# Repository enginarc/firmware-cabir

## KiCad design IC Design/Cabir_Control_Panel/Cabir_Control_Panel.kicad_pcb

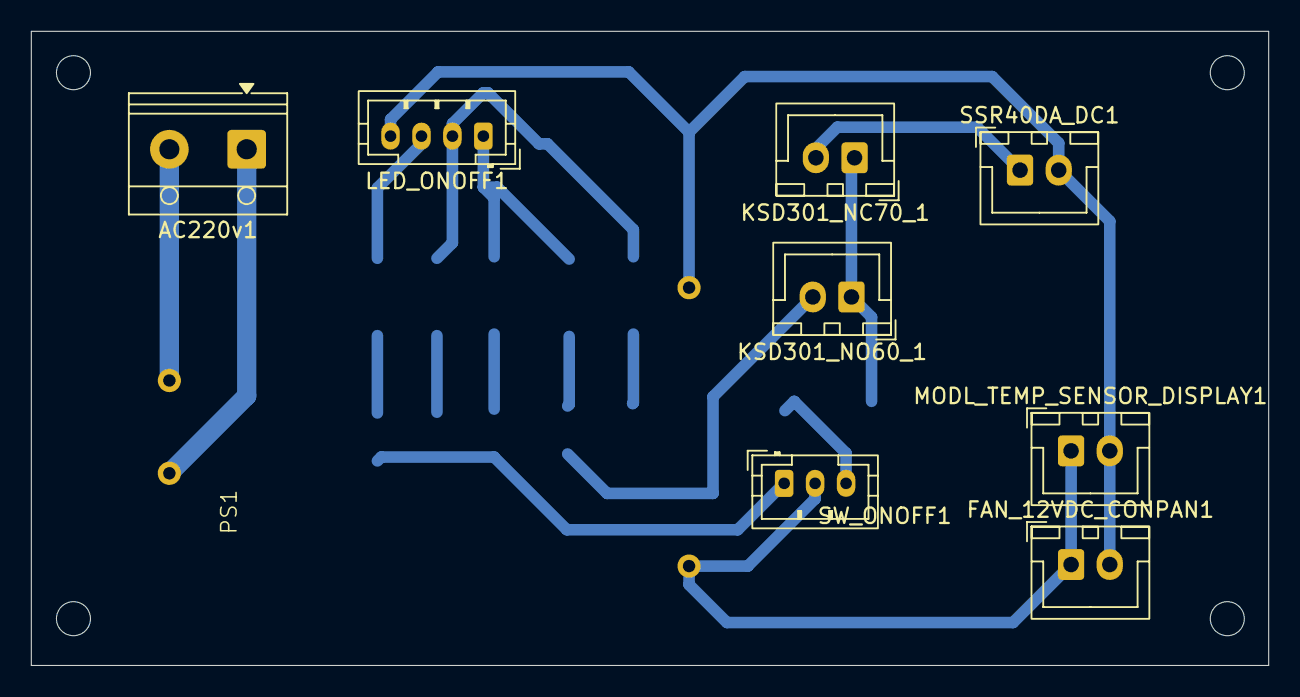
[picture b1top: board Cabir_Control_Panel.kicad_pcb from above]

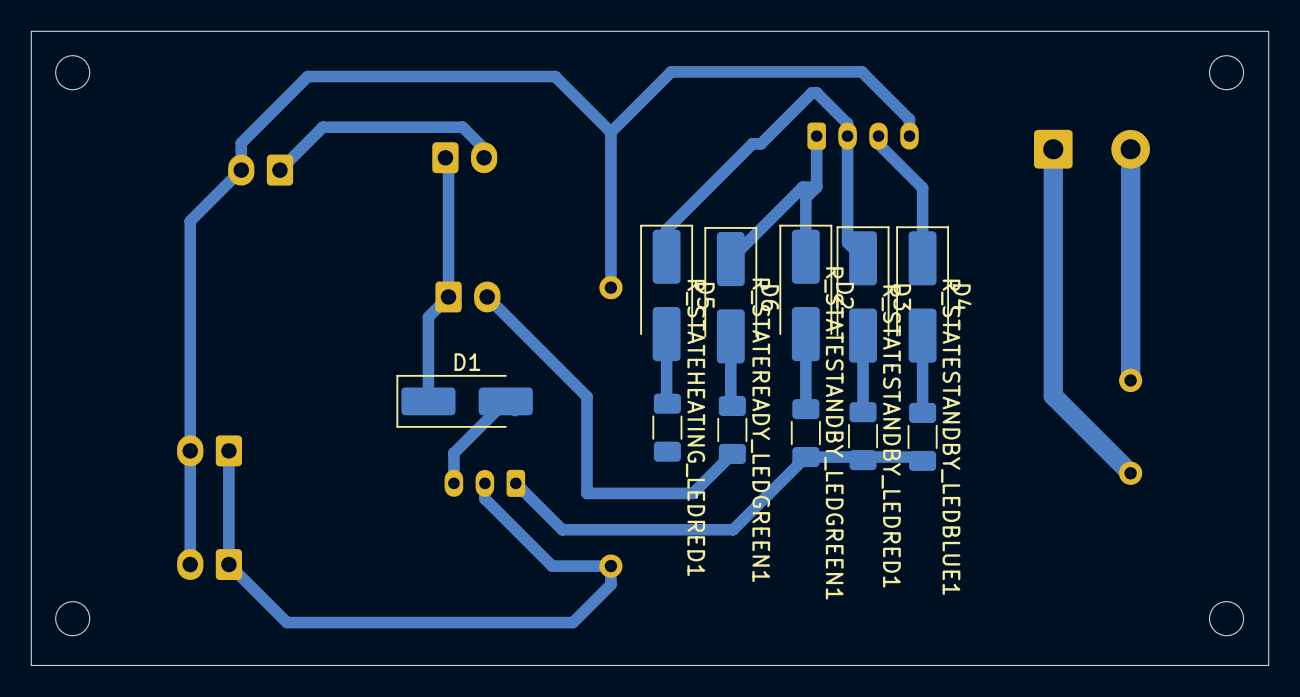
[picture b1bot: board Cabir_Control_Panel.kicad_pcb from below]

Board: 2 copper layers, 80.0 x 41.0 mm, 20 parts (11 on the bottom side), 17 nets.

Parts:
AC220v1: Screw_Terminal_01x02; TerminalBlock_RND_205-00012_1x02_P5.00mm_Horizontal
D1, D2, D3, D4, D5, D6: M7; D_SMA_Handsoldering
FAN_12VDC_CONPAN1: Conn_01x02_Pin; JST_XH_B2B-XH-A_1x02_P2.50mm_Vertical
KSD301_NC70_1, KSD301_NO60_1: Conn_01x02_Pin; JST_XH_B2B-XH-A_1x02_P2.50mm_Vertical
LED_ONOFF1: Conn_01x04_Pin; JST_PH_B4B-PH-K_1x04_P2.00mm_Vertical
MODL_TEMP_SENSOR_DISPLAY1: Conn_01x02_Pin; JST_XH_B2B-XH-A_1x02_P2.50mm_Vertical
PS1: HLK-5M12_PCB_AC-DC_Adapter
R_STATEHEATING_LEDRED1: 470R; R_1206_3216Metric_Pad1.30x1.75mm_HandSolder
R_STATEREADY_LEDGREEN1: 470R; R_1206_3216Metric_Pad1.30x1.75mm_HandSolder
R_STATESTANDBY_LEDBLUE1: 1.2k; R_1206_3216Metric_Pad1.30x1.75mm_HandSolder
R_STATESTANDBY_LEDGREEN1: 470R; R_1206_3216Metric_Pad1.30x1.75mm_HandSolder
R_STATESTANDBY_LEDRED1: 470R; R_1206_3216Metric_Pad1.30x1.75mm_HandSolder
SSR40DA_DC1: Conn_01x02_Pin; JST_XH_B2B-XH-A_1x02_P2.50mm_Vertical
SW_ONOFF1: Conn_01x03_Pin; JST_PH_B3B-PH-K_1x03_P2.00mm_Vertical

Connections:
/12V+: FAN_12VDC_CONPAN1.1, MODL_TEMP_SENSOR_DISPLAY1.1, PS1.4 (+Vout), SW_ONOFF1.2
/BLUE+: D4.1 (K), LED_ONOFF1.3
/GREEN+: D2.1 (K), D6.1 (K), LED_ONOFF1.1
/OFF+: R_STATESTANDBY_LEDBLUE1.2, R_STATESTANDBY_LEDGREEN1.2, R_STATESTANDBY_LEDRED1.2, SW_ONOFF1.1
/ON+: D1.2 (A), SW_ONOFF1.3
/RED+: D3.1 (K), D5.1 (K), LED_ONOFF1.2
GND: FAN_12VDC_CONPAN1.2, LED_ONOFF1.4, MODL_TEMP_SENSOR_DISPLAY1.2, PS1.3 (-Vout), SSR40DA_DC1.2
unnamed: AC220v1.2, PS1.1 (AC_(L))
unnamed: AC220v1.1, PS1.2 (AC_(N))
unnamed: D1.1 (K), KSD301_NC70_1.1, KSD301_NO60_1.1
unnamed: D2.2 (A), R_STATESTANDBY_LEDGREEN1.1
unnamed: D3.2 (A), R_STATESTANDBY_LEDRED1.1
unnamed: D4.2 (A), R_STATESTANDBY_LEDBLUE1.1
unnamed: D5.2 (A), R_STATEHEATING_LEDRED1.1
unnamed: D6.2 (A), R_STATEREADY_LEDGREEN1.1
unnamed: KSD301_NC70_1.2, R_STATEHEATING_LEDRED1.2, SSR40DA_DC1.1
unnamed: KSD301_NO60_1.2, R_STATEREADY_LEDGREEN1.2

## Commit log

2026-04-12 Initial
2026-04-12 sdconfig changes.
2026-04-12 first run without issues
2026-04-13 Add Unique suffix to Device name for distinction
2026-04-21 Circuit design - initial
2026-04-21 Remove IC Design
